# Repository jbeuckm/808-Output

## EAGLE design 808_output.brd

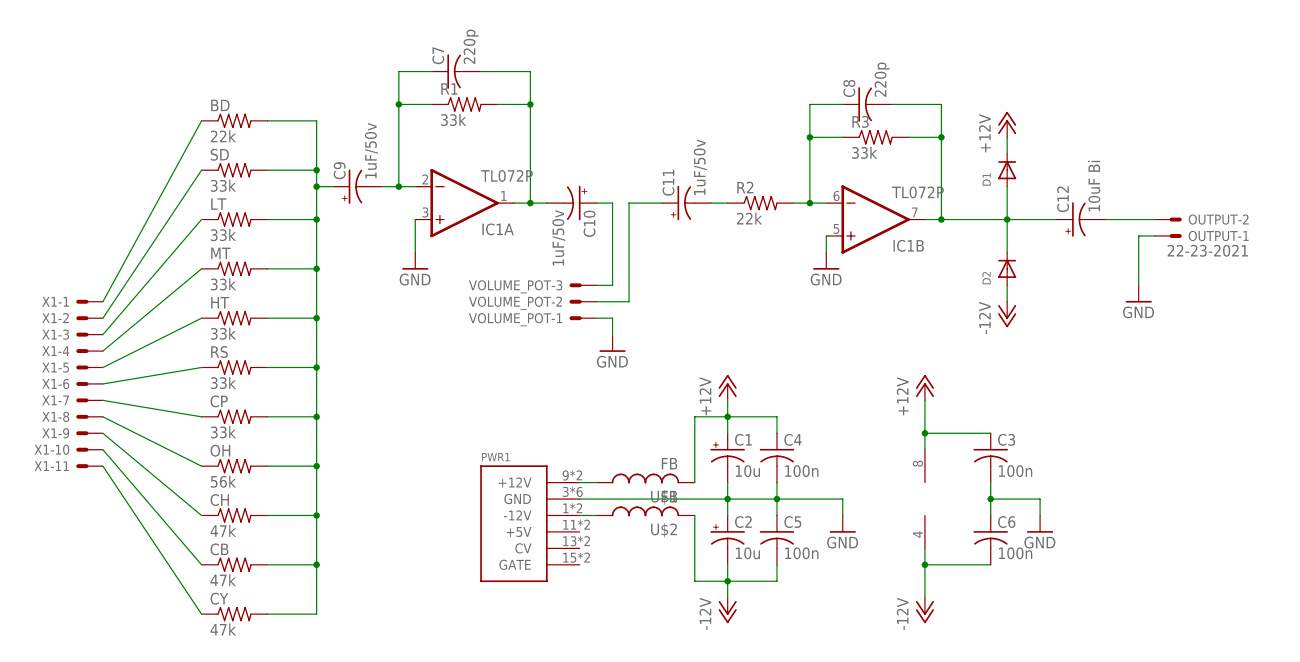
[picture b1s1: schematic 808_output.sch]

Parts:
BD: 22k; 0207/5V
C1, C2: 10u; B45181A
C3, C4, C5, C6: 100n; C050-024X044
C7, C8: 220p; C025-025X050
C9, C10, C11: 1uF/50v; B45181A
C12: 10uF Bi; B45181A
CB: 47k; 0207/5V
CH: 47k; 0207/5V
CP: 33k; 0207/5V
CY: 47k; 0207/5V
D1, D2: DIODEDO-1N4148; DO-1N4148
HT: 33k; 0207/5V
IC1: TL072P; DIL08
LT: 33k; 0207/5V
MT: 33k; 0207/5V
OH: 56k; 0207/5V
OUTPUT: 22-23-2021
PWR1: POWER; POWER_16
R1, R3: 33k; 0207/7
R2: 22k; 0207/7
RS: 33k; 0207/5V
SD: 33k; 0207/5V
U$1, U$2: FB
VOLUME_POT: KK-156-3
X1: KK-156-11

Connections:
+12V: C1.+, C3.1, C4.1, D1.C, IC1.8 (V+), U$1.P$2 (2)
-12V: C2.-, C5.2, C6.2, D2.A, IC1.4 (V-), U$2.P$2 (2)
GND: C1.-, C2.+, C3.2, C4.2, C5.1, C6.1, IC1.3 (+IN), IC1.5 (+IN), OUTPUT.1, PWR1.3 (GND), PWR1.4 (GND), PWR1.5 (GND), PWR1.6 (GND), PWR1.7 (GND), PWR1.8 (GND), VOLUME_POT.1
unnamed: PWR1.9 (+12V), PWR1.10 (+12V), U$1.P$1 (1)
unnamed: PWR1.1 (-12V), PWR1.2 (-12V), U$2.P$1 (1)
unnamed: BD.1, X1.1
unnamed: SD.1, X1.2
unnamed: LT.1, X1.3
unnamed: MT.1, X1.4
unnamed: HT.1, X1.5
unnamed: RS.1, X1.6
unnamed: CP.1, X1.7
unnamed: OH.1, X1.8
unnamed: CH.1, X1.9
unnamed: CB.1, X1.10
unnamed: CY.1, X1.11
unnamed: BD.2, C9.+, CB.2, CH.2, CP.2, CY.2, HT.2, LT.2, MT.2, OH.2, RS.2, SD.2
unnamed: C7.2, C10.-, IC1.1 (OUT), R1.2
unnamed: C8.1, IC1.6 (-IN), R2.2, R3.1
unnamed: C7.1, C9.-, IC1.2 (-IN), R1.1
unnamed: C11.-, R2.1
unnamed: C8.2, C12.+, D1.A, D2.C, IC1.7 (OUT), R3.2
unnamed: C10.+, VOLUME_POT.3
unnamed: C11.+, VOLUME_POT.2
unnamed: C12.-, OUTPUT.2

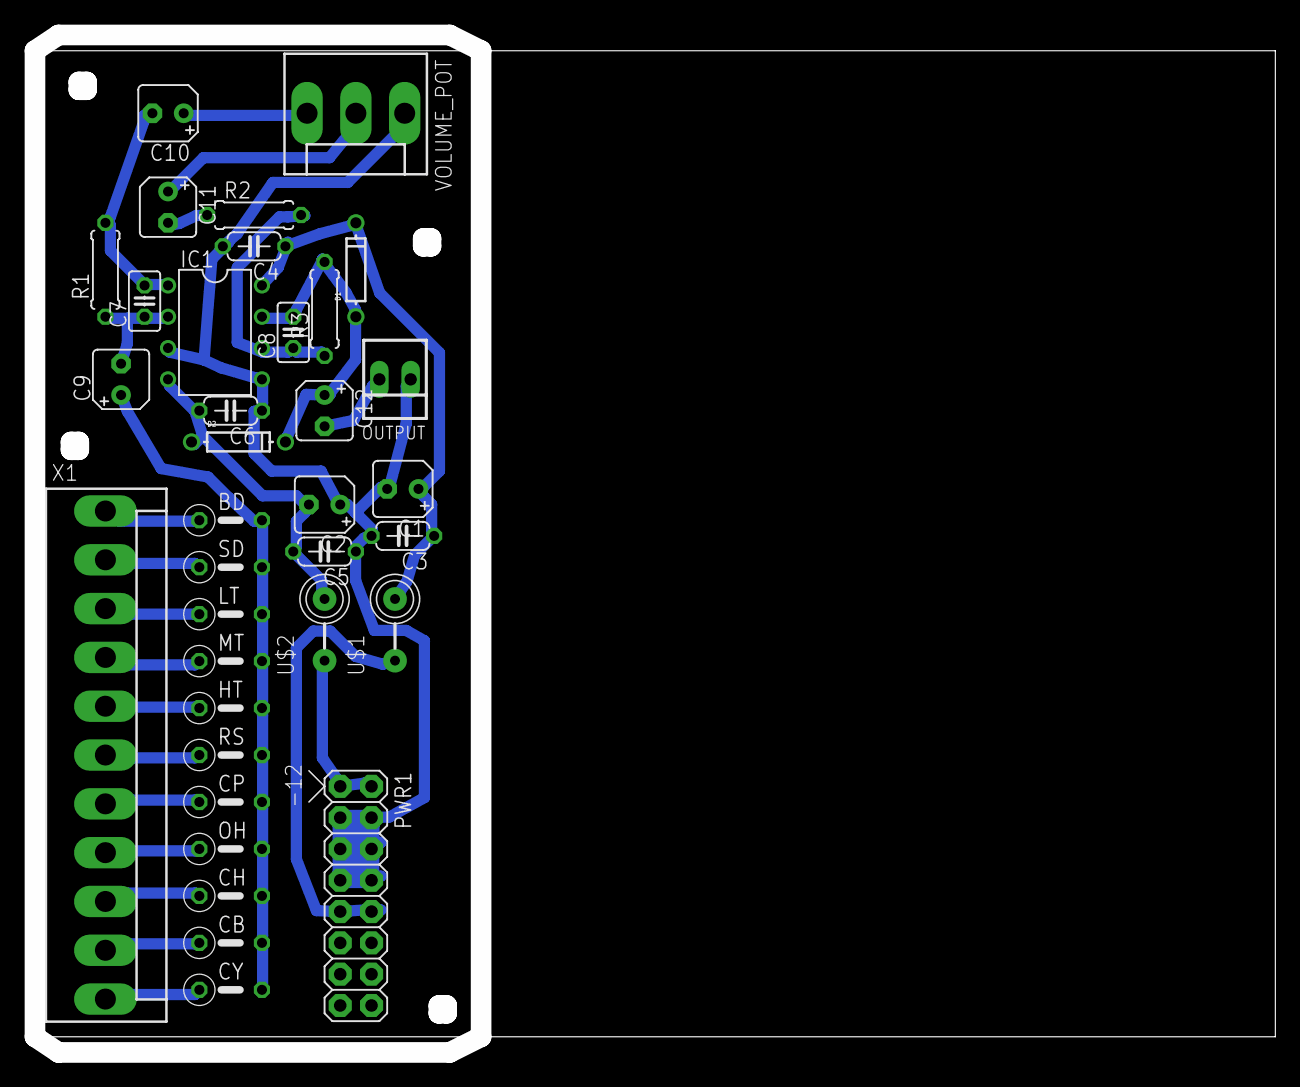
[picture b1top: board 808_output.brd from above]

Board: 2 copper layers, 99.8 x 82.5 mm, 35 parts (0 on the bottom side), 25 nets.

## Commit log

2016-04-27 layout
2016-04-28 closer to og 808
2016-04-28 routed
2016-04-28 tweaks
2016-04-29 gcode
